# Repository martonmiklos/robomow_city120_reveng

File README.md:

# General parameters of the Robomow RL-2000 (City 120) robot - user terminal communication
 * 0-5V levels between the PIC in the terminal and the H8S/2000 in the robot
 * 19200 baud 8n1 inverted (UART idles at low)
 * Checksum: sum all bytes then negate
 * For RJ12 pinout see the [revenged schematics](https://github.com/martonmiklos/robomow_city120_reveng/blob/master/robomow_city120_terminal.sch)
 
 J105 pinout:
 RX1: 4
 TX1: 5
 RX0: 2
 TX0: 3
 GND: 8
 
# Terminal response packets

Terminal sends the following packets periodically (with varying -depending on the traffic from the robot- rate between 10-60ms). 
I never saw traffic on the TX and RX at the same time (the terminal and the robot seems to be handshaking on the bus).

```
* Idle:     0x23 0x00 0x18 0xC4
* Forward:  0x23 0x40 0x18 0x84
* Backward: 0x23 0x80 0x18 0x44
* Left:     0x23 0x10 0x18 0xB4
* Right:    0x23 0x20 0x18 0xA4
* Rabbit:   0x23 0x00 0x19 0xC3
* C:        0x23 0x08 0x18 0xBC
* Go:       0x23 0x04 0x18 0x44
* Stop:     0x23 0x00 0x1A 0xC2
* Factory:  0x23 0x00 0x1C 0xC0
* Up:       0x23 0x01 0x18 0xC3
* Down:     0x23 0x02 0x18 0xC2
```

# HW reverse engineering info

I currently have the following boards:
* ESB0019B04 - broken
* ESB0050D - broken
* ESB0100D - likely new

## H8S MCU mode strapping

Strapped to Mode 5
- MD0 VCC
- MD1 GND
- MD2 VCC

## I2C EEPROM

SDA - P53
SCL - P52

## External RAM

64KByte

## Current limit on motors

Shunts wired to LM393-s which output is read via 74HC153 muxes, mapping of them is TBD

# Firmware reversing info

## RAM

### Internal RAM
2K on chip RAM present between 0xFFF400 to 0xFFFC00

### External RAM

128K x 8

- ESB0019B04 - V62C5181024LL-35W
- ESB0050D Samsung K6X1008C2D-BF-55
- ESB0100D Cypress CY62128LL

The contents of the external RAM is initialized from the flash in multiple portions

- ROM 0x01007E-0x0101F2 copied to RAM 0x221140-0x2212B4 (372 byte)
- ROM 0x010570-0x0113A8 copied to RAM 0x2212B4-0x2220EC (3640 byte)

## UART 0

UART0 is connected to the terminal, has 31 byte RX buffer

### UART 1

The UART1 is initialized to 4800 baud (F_CPU == 16M, BRR1 == 103), the baud rate is adjustable with some commands.

Physically this UART is wired to this connector:

The UART1 looks to have simpler protocol, and it might be involved in bootloader/flashing/config upload activites (it ends in one case using a "DownLoad..." string).

### UART1 protocol info

The following info gathere by analyzing the 4.33 City-120 firmware in IDA.

Never tested it due ot the danger insisted by the DownLoad string.

0. byte: 
    if 0xAA - process the 6. byte
    if 0x83, 0x87, 0x89 - next byte needs to be 'm'
    if 0xC4 - process the 3. byte
    if 0x68 - (ascii 'h') the activates some sort of 
1. byte: if not 'm' (0x6D) then reset processing for 0x83, 0x87, 0x89
2. byte
    if 0x83, 0x87 then proceeds to some section leading to a DownLoad string.
3. byte
    if 0xC5 - follows processing
    else - resets packet processing
4. byte
    if 0xC7 - perform BIST
5. byte
    itt meghívódik egy komolyabb függvény
6. byte
    eltároljuk -> 7.re

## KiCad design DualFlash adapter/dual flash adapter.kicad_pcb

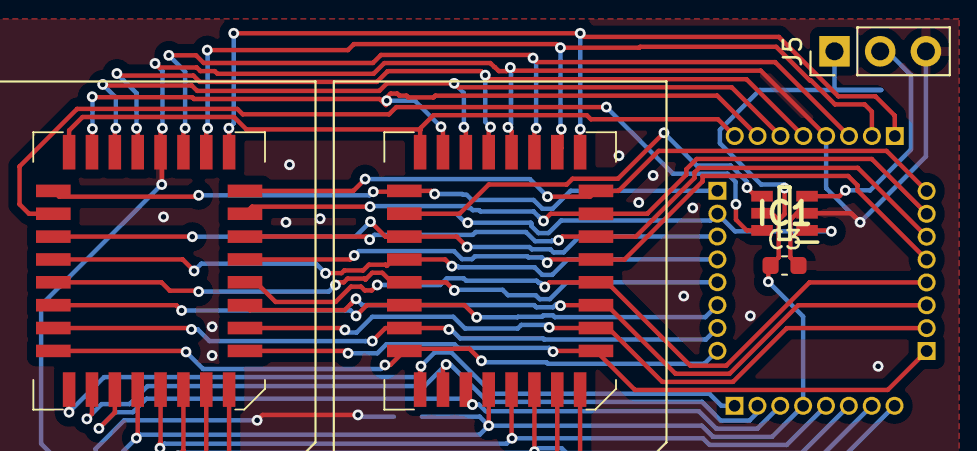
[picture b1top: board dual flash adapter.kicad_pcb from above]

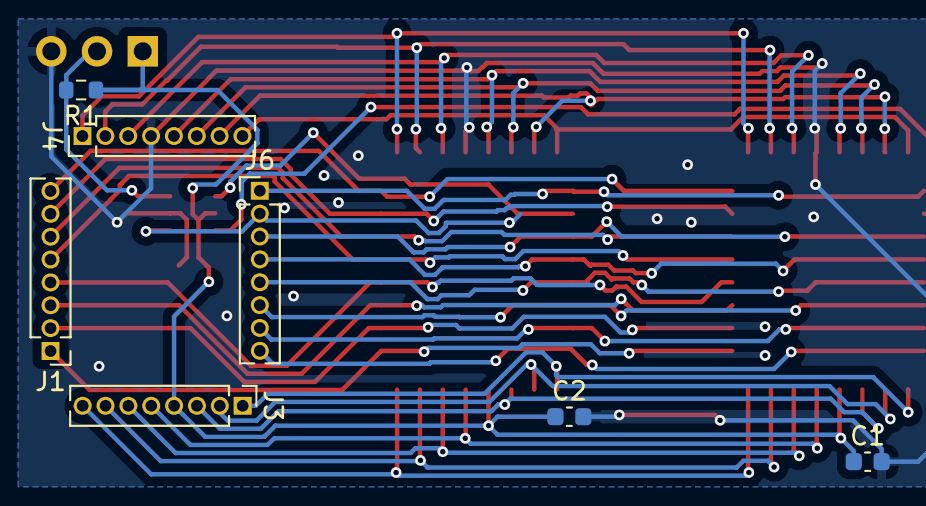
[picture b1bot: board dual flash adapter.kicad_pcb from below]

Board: 2 copper layers, 12 parts (7 on the bottom side), 35 nets.

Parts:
C1, C2, C3: 100nF; C_0603_1608Metric
IC1: SN74LVC1G19DBVRE4; SOT95P280X145-6N
J1, J3, J4, J6: Conn_01x08; PinHeader_1x08_P1.27mm_Vertical
J5: Conn_01x03; PinHeader_1x03_P2.54mm_Vertical
R1: 10K; R_0603_1608Metric
U1, U2: Am29F040; PLCC-32_SMD-Socket

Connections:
/CE_SELECT_CONN: IC1.3 (~E), J5.2, R1.2
/P1: J3.5, U1.1 (A18), U2.1 (A18)
/P2: J3.6, U1.2 (A16), U2.2 (A16)
/P3: J3.7, U1.3 (A15), U2.3 (A15)
/P4: J3.8, U1.4 (A12), U2.4 (A12)
/P5: J1.1, U1.5 (A7), U2.5 (A7)
/P6: J1.2, U1.6 (A6), U2.6 (A6)
/P7: J1.3, U1.7 (A5), U2.7 (A5)
/P8: J1.4, U1.8 (A4), U2.8 (A4)
/P9: J1.5, U1.9 (A3), U2.9 (A3)
/P10: J1.6, U1.10 (A2), U2.10 (A2)
/P11: J1.7, U1.11 (A1), U2.11 (A1)
/P12: J1.8, U1.12 (A0), U2.12 (A0)
/P13: J4.1, U1.13 (DQ0), U2.13 (DQ0)
/P14: J4.2, U1.14 (DQ1), U2.14 (DQ1)
/P15: J4.3, U1.15 (DQ2), U2.15 (DQ2)
/P17: J4.5, U1.17 (DQ3), U2.17 (DQ3)
/P18: J4.6, U1.18 (DQ4), U2.18 (DQ4)
/P19: J4.7, U1.19 (DQ5), U2.19 (DQ5)
/P20: J4.8, U1.20 (DQ6), U2.20 (DQ6)
/P21: J6.1, U1.21 (DQ7), U2.21 (DQ7)
/P23: J6.3, U1.23 (A10), U2.23 (A10)
/P24: J6.4, U1.24 (~OE), U2.24 (~OE)
/P25: J6.5, U1.25 (A11), U2.25 (A11)
/P26: J6.6, U1.26 (A9), U2.26 (A9)
/P27: J6.7, U1.27 (A8), U2.27 (A8)
/P28: J6.8, U1.28 (A13), U2.28 (A13)
/P29: J3.1, U1.29 (A14), U2.29 (A14)
/P30: J3.2, U1.30 (A17), U2.30 (A17)
/P31: J3.3, U1.31 (~WE), U2.31 (~WE)
/~CE: IC1.1 (A), J6.2
CE1: IC1.6 (Y0), U1.22 (~CE)
CE2: IC1.4 (Y1), U2.22 (~CE)
GND: C1.2, C2.2, C3.2, IC1.2 (GND), J4.4, J5.3, U1.16 (GND), U2.16 (GND)
VCC: C1.1, C2.1, C3.1, IC1.5 (VCC), J3.4, J5.1, R1.1, U1.32 (VCC), U2.32 (VCC)

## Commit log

2019-06-20 Add sch
2019-06-20 Add other stuff
2019-07-08 Added logs, revenged terminal commands
2019-08-10 Added flash dump
2020-05-30 Added logs from RM toolkit (City 110 TX logs)
2020-06-01 README update
2021-04-14 Update README.md
    Added reveng info
2021-04-23 Added H8S 2350 register definition IDA script
2021-11-02 Update README.md
    Fixup go command
2022-04-24 Added perimeter schematic
2025-05-02 Upload reveng infos
2025-05-02 Daily save
2025-05-04 Board routed
2025-05-08 Add RAM types
2025-08-20 Repo update
2025-08-21 Add controller window plexi for lasercut
2025-08-30 Add bumper an slippage sensor connections
2026-06-30 Add new backup files
2026-06-30 Rename
2026-06-30 Remove renamed files
